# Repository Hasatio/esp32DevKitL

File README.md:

# ESP32-DEVKIT-L

The circuit taken as an example while designing the board [Olimex ESP32-Gateway](https://www.olimex.com/Products/IoT/ESP32/ESP32-GATEWAY)

## Revision 0

### Added:
- 1x TCA9548 mux IC
- 8x QWIIC connector
- 2x2 Molex connector for for external power supply
- 1x K7805-2000R3L or K7805-2000R3 for 5v convert
- Logo

### Changed:
- Type C
- ESP32-WROOM-32D model
- K7803-2000R3L or K7803-2000R3 for 5V to 3.3V convert
- Texts in pinout

## Revision 1

### Added:
- QWIIC connector pinout

## Revision 2

### Changed:
- Led GPIO33 to GPIO35
- PCA9548's SDA pin GPIO16 to GPIO33

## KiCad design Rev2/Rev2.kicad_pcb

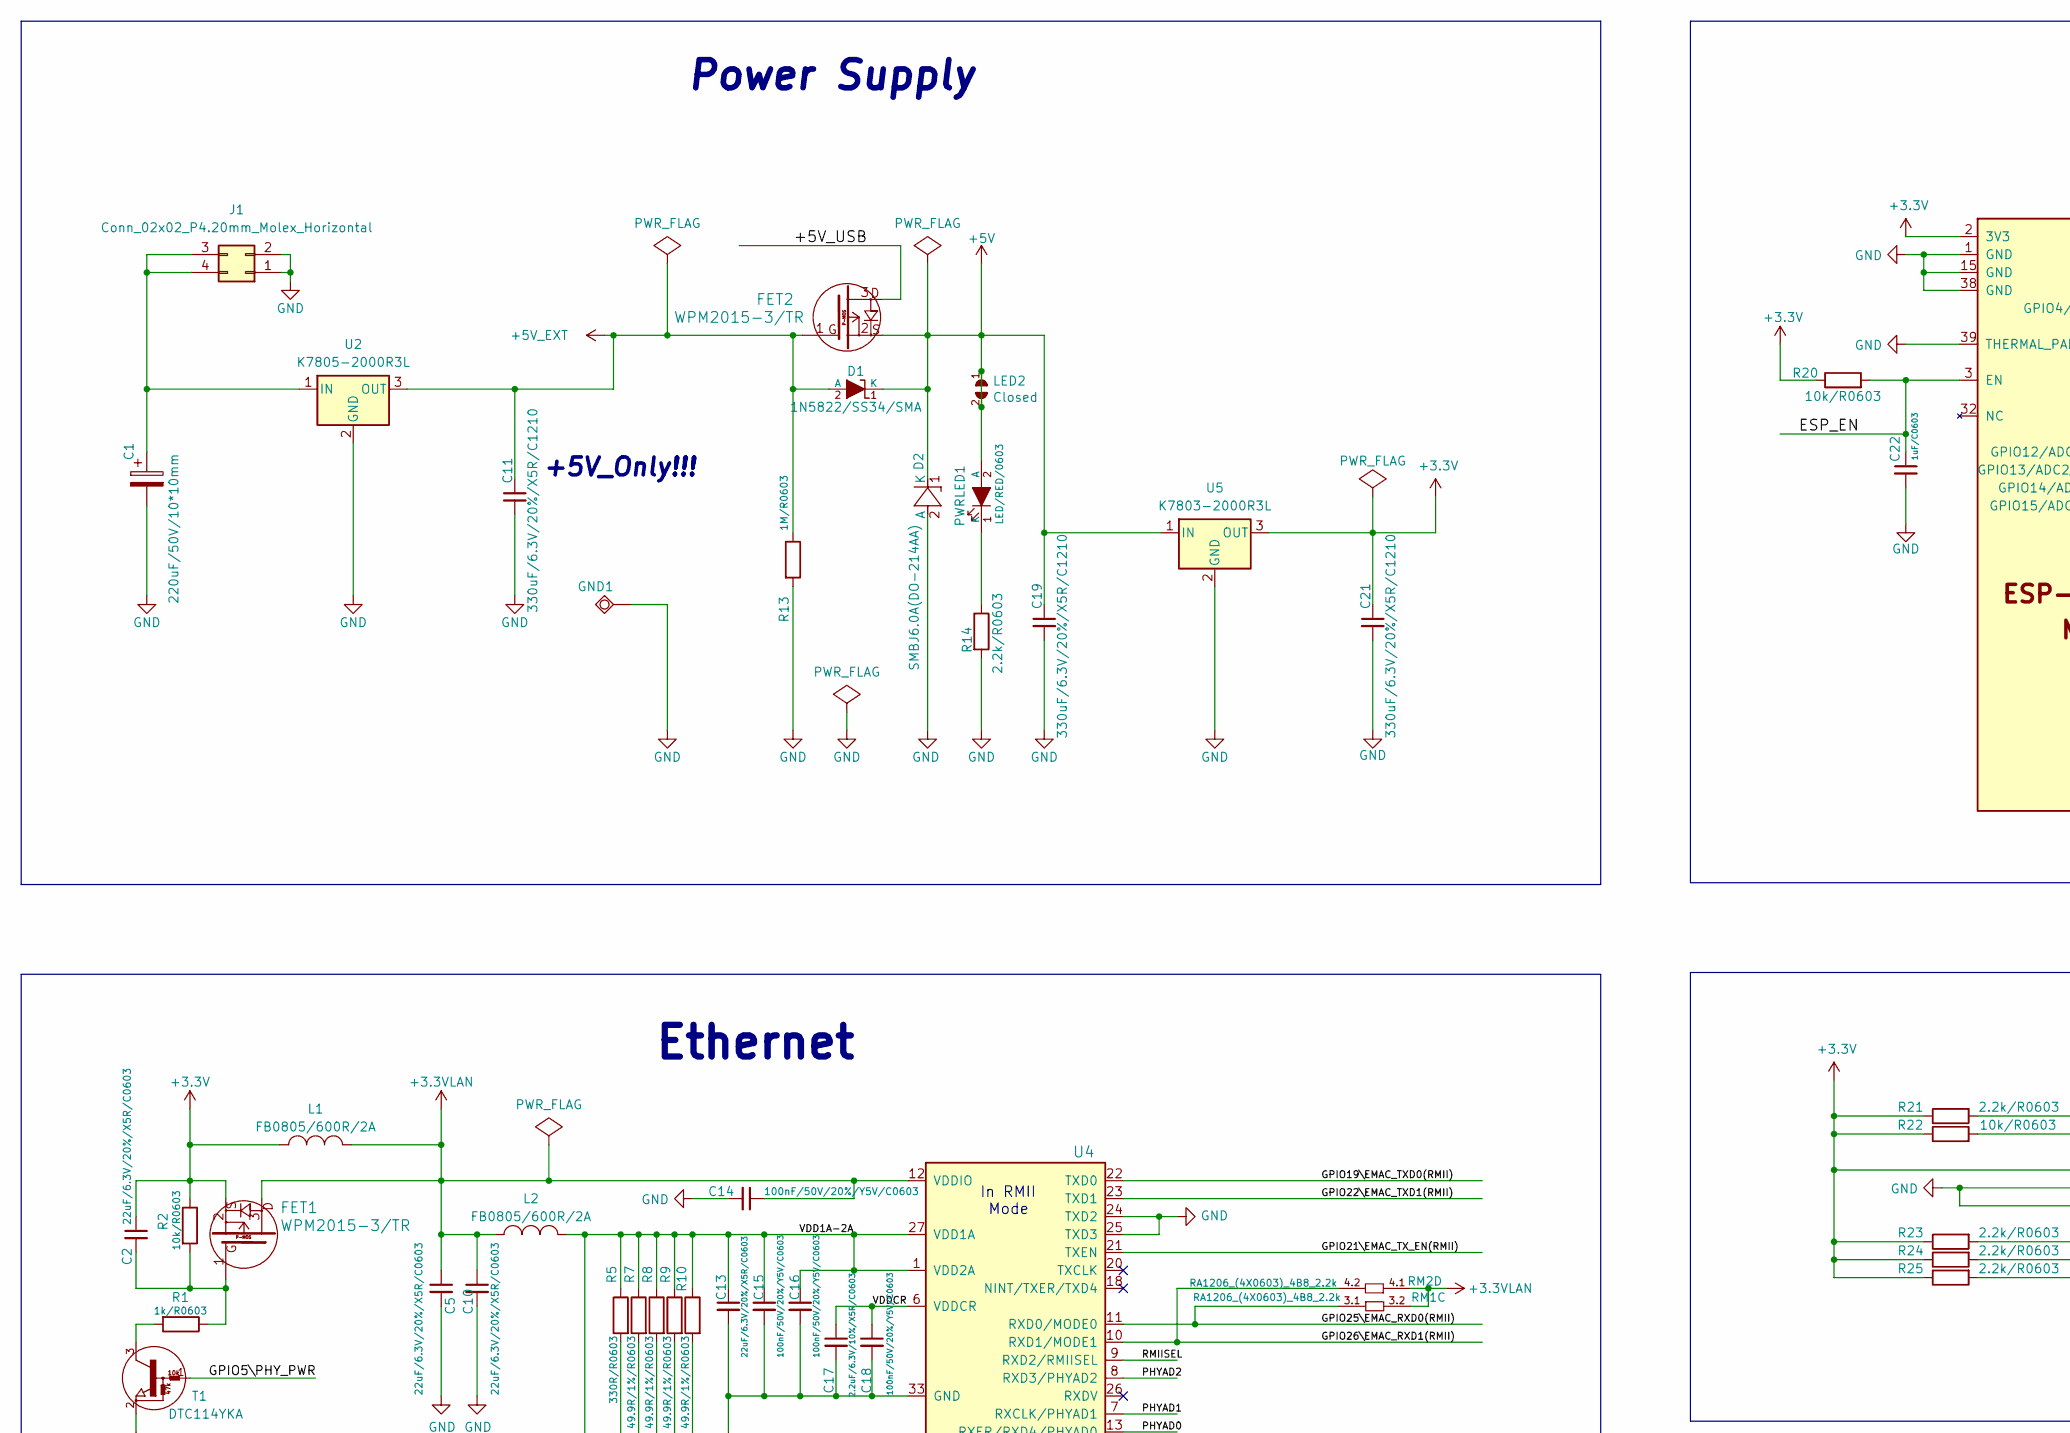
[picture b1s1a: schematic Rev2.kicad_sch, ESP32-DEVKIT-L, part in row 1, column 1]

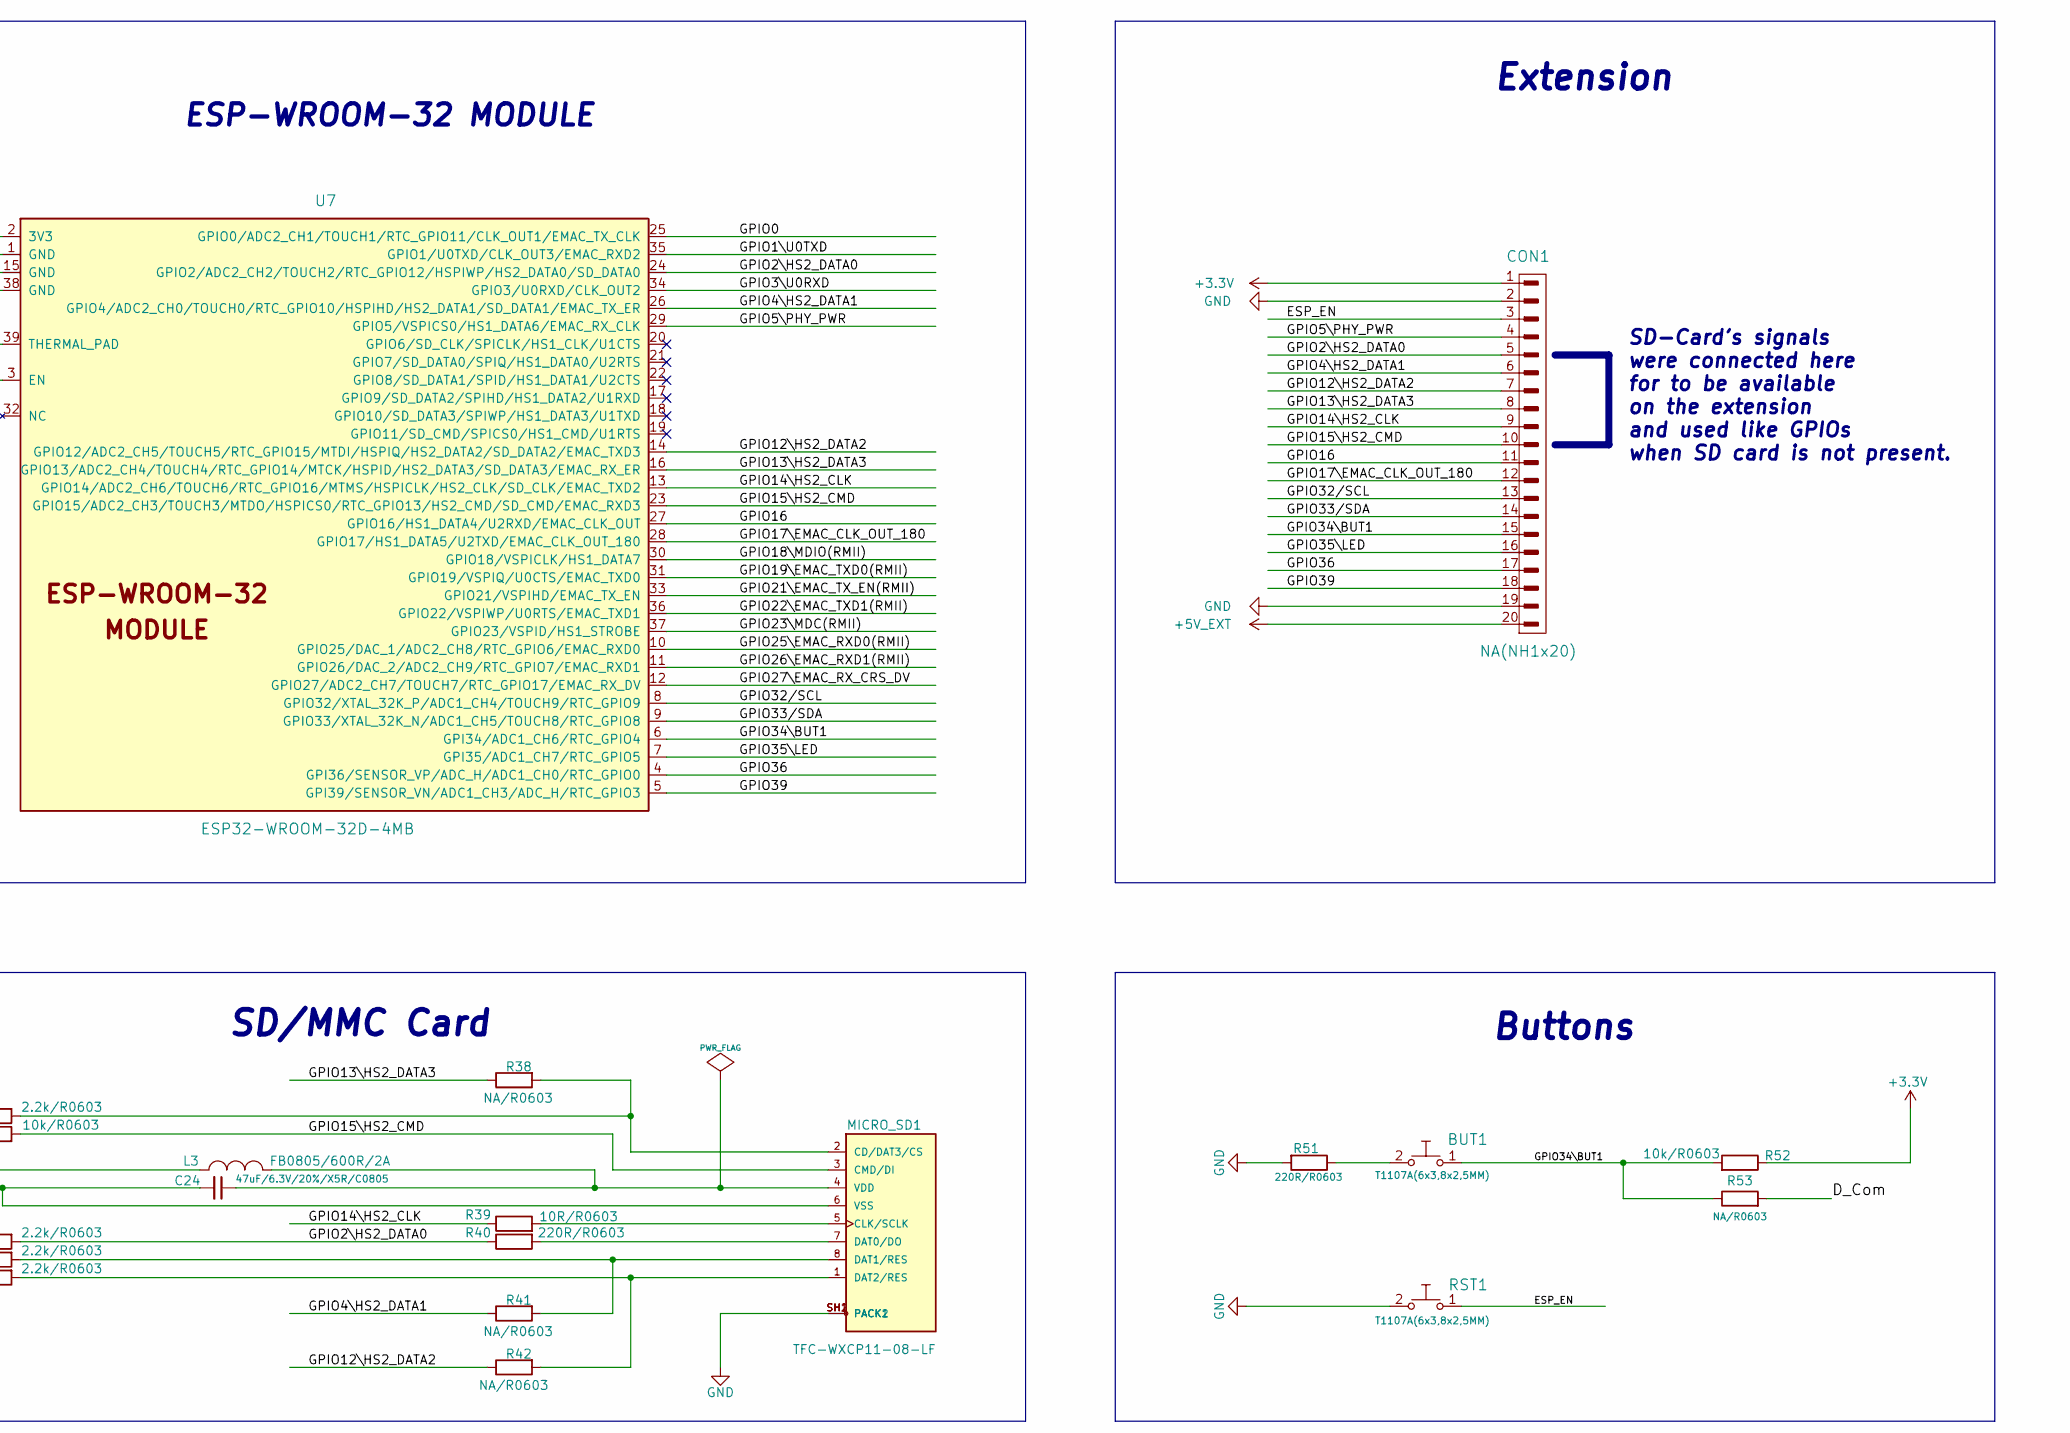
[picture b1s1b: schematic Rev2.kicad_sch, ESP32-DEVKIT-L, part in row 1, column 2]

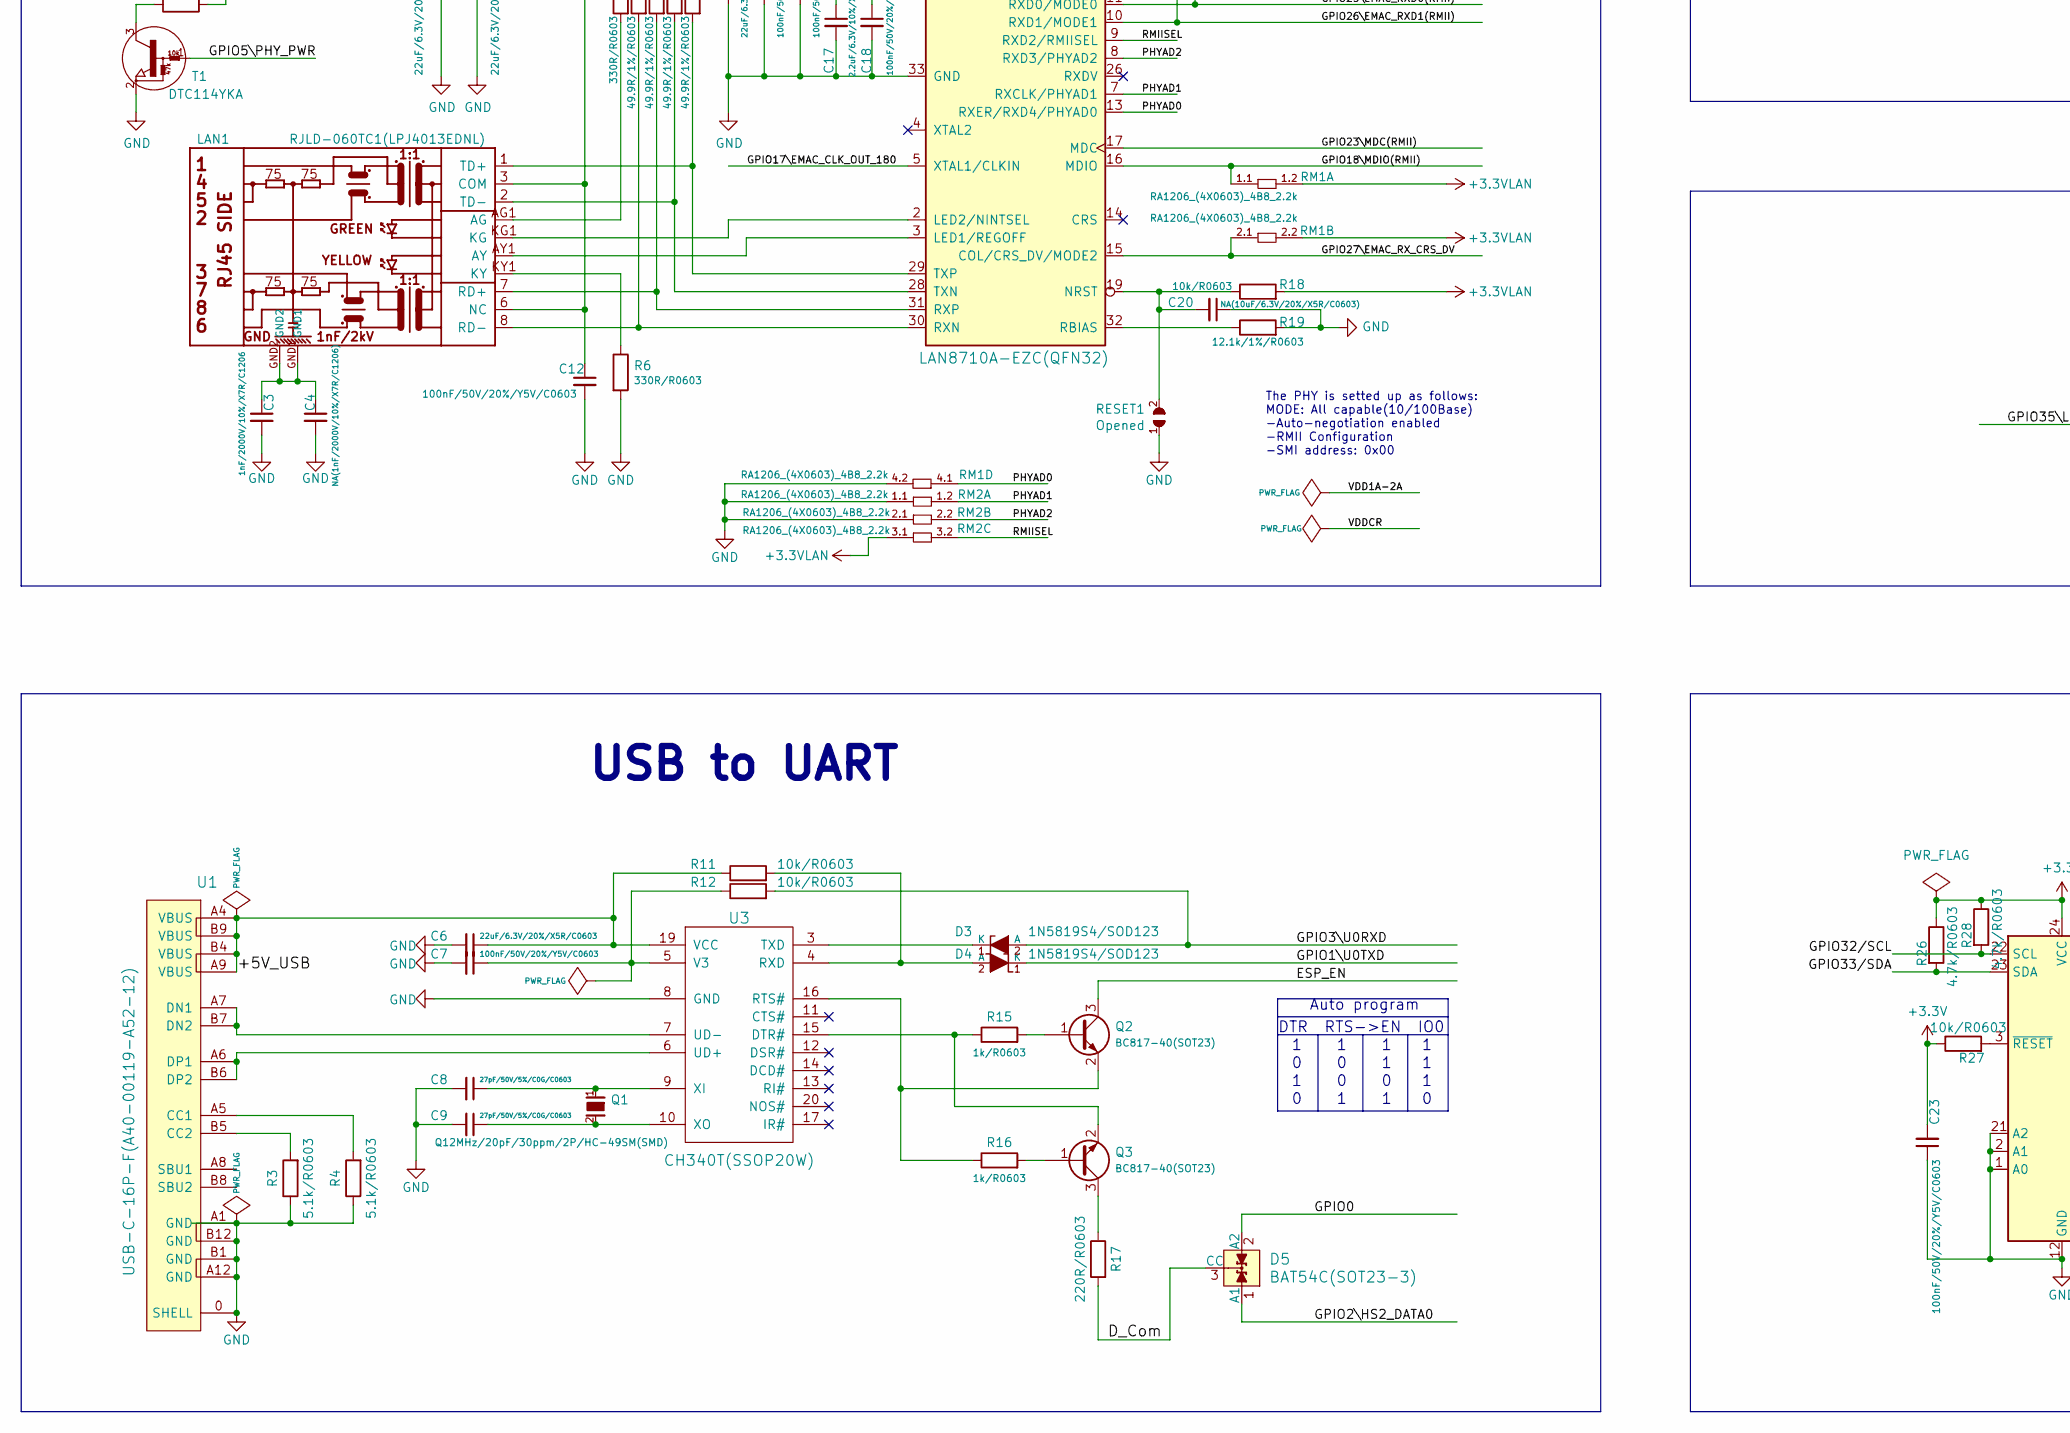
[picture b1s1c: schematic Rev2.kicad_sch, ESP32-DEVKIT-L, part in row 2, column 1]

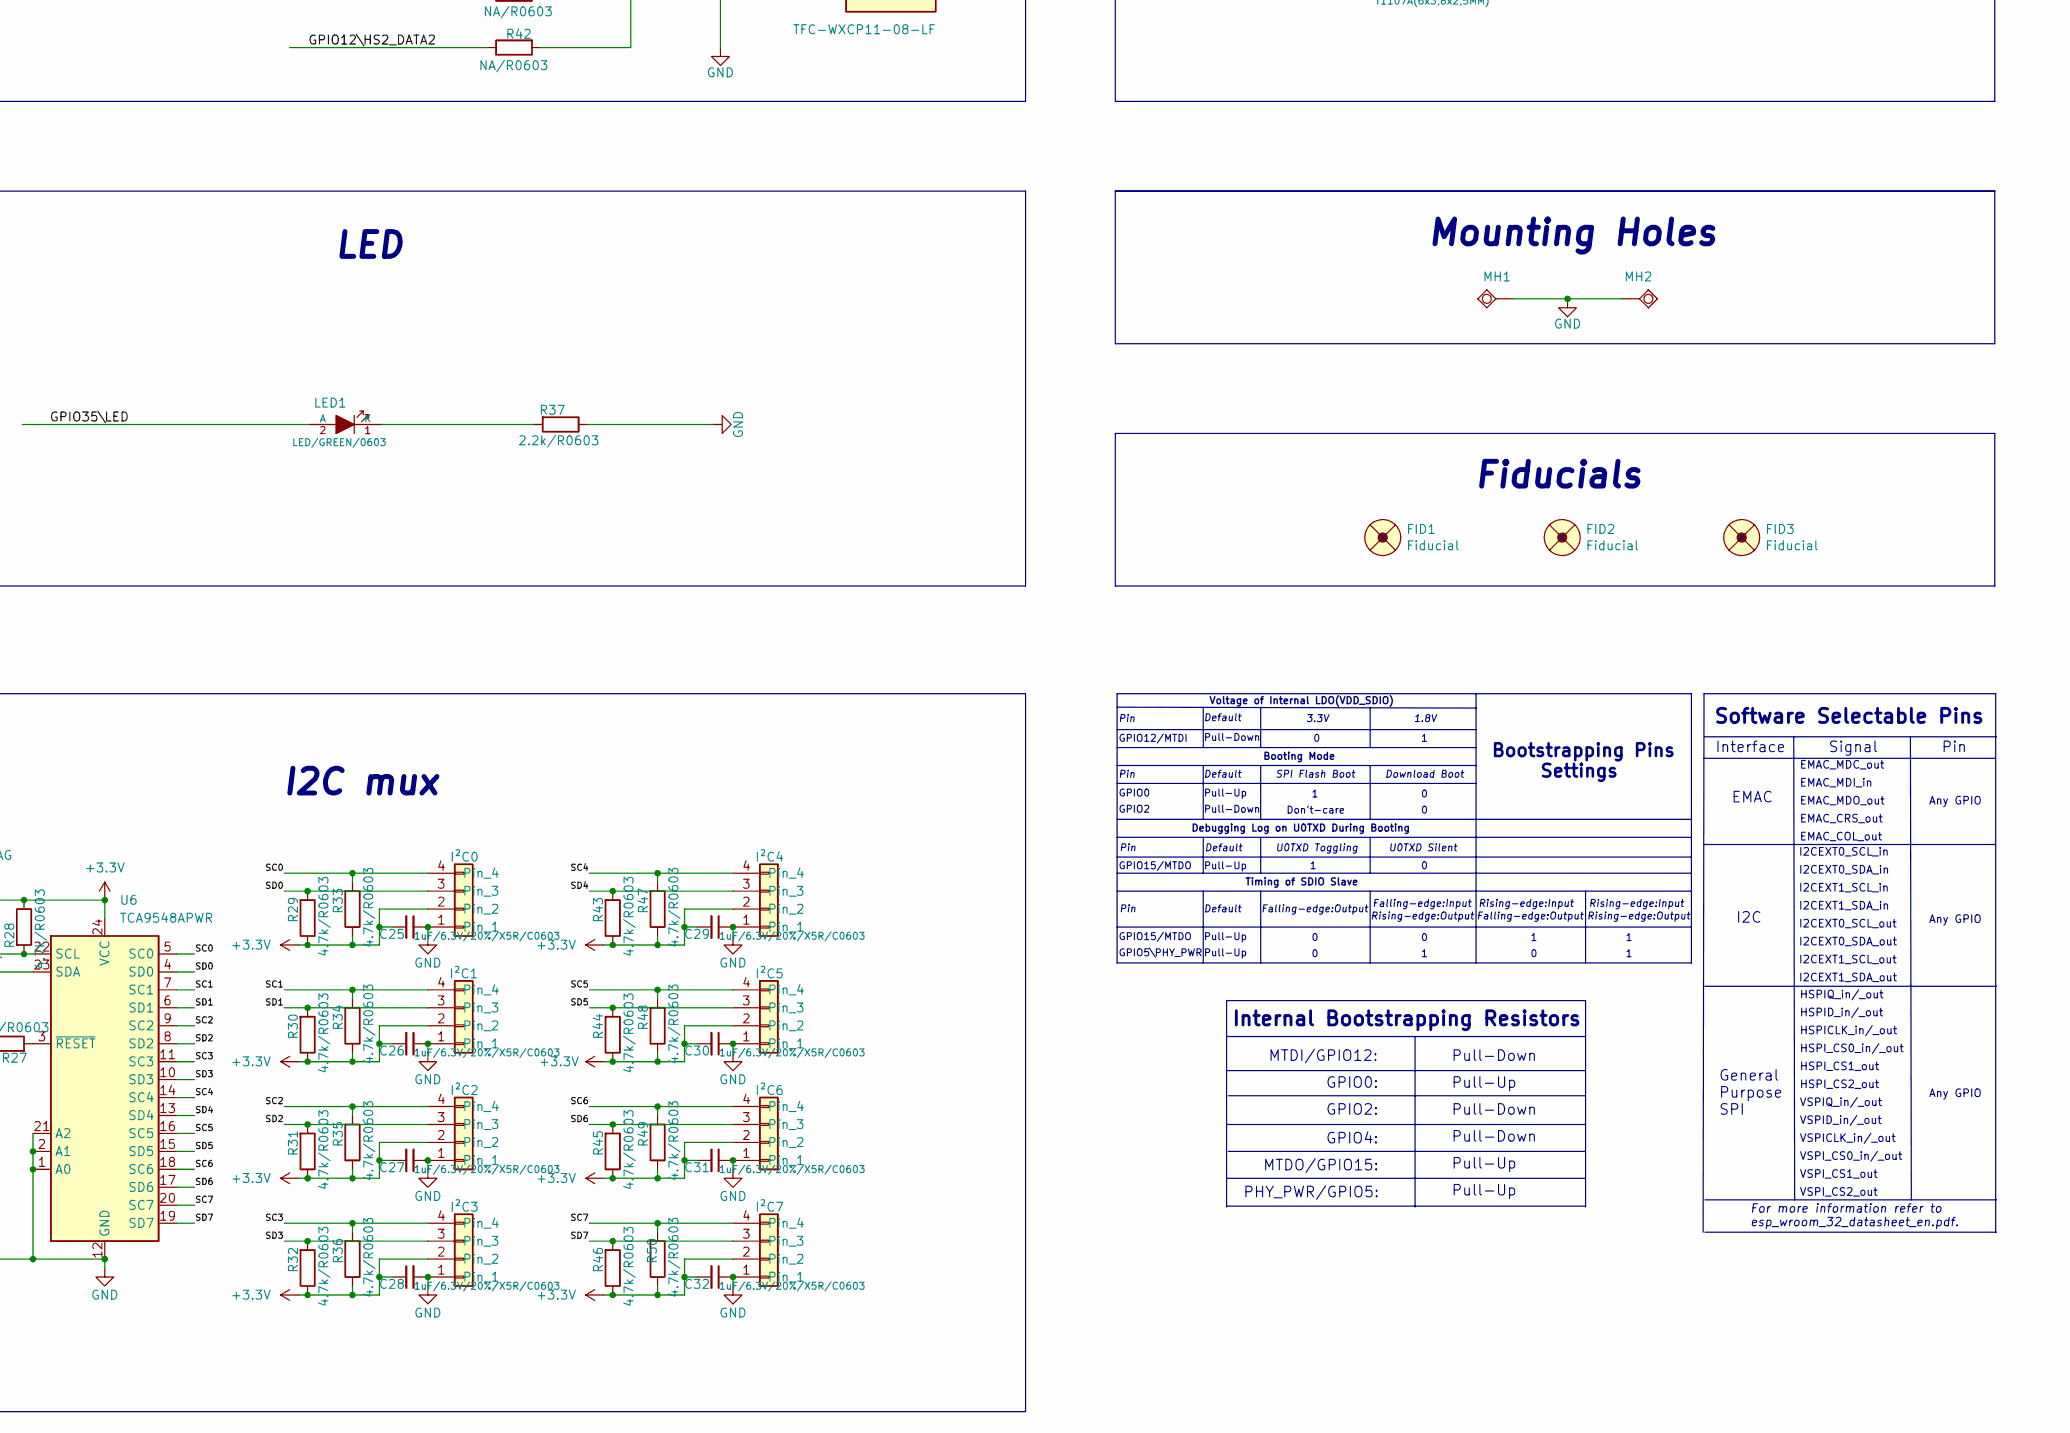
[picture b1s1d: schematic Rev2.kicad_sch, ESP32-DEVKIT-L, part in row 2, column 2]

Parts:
BUT1: T1107A(6x3,8x2,5MM)
C1: 220uF/50V/10*10mm; CP_Elec_10x10.5
C2, C5, C6, C10, C13: 22uF/6.3V/20%/X5R/C0603; 0603
C3: 1nF/2000V/10%/X7R/C1206; 1206
C4: NA(1nF/2000V/10%/X7R/C1206); 1206
C7, C12, C14, C15, C16, C18, C23: 100nF/50V/20%/Y5V/C0603; 0603
C8, C9: 27pF/50V/5%/C0G/C0603; 0603
C11, C19, C21: 330uF/6.3V/20%/X5R/C1210; 1210
C17: 2.2uF/6.3V/10%/X5R/C0603; 0603
C20: NA(10uF/6.3V/20%/X5R/C0603); 0603
C22: 1uF/C0603; 0603
C24: 47uF/6.3V/20%/X5R/C0805; 0805
C25, C26, C27, C28, C29, C30, C31, C32: 1uF/6.3V/20%/X5R/C0603; 0603
CON1: NA(NH1x20); HN1x20
D1: 1N5822/SS34/SMA; SMA-KA
D2: SMBJ6.0A(DO-214AA); DO214AA_1(K)-2(A)
D3, D4: 1N5819S4/SOD123; SOD-123_1C-2A_KA
D5: BAT54C(SOT23-3); SOT23-3
FET1, FET2: WPM2015-3/TR; SOT23
FID1, FID2, FID3: Fiducial; Fiducial1x3
GND1: TESTPAD; TESTPAD_40-ROUND
I²C0, I²C1, I²C2, I²C3, I²C4, I²C5, I²C6, I²C7: Conn_01x04_P1.00mm_Stemma qt/Qwiic; JST_SH_SM04B-SRSS-TB_1x04-1MP_P1.00mm_Horizontal
J1: Conn_02x02_P4.20mm_Molex_Horizontal; Molex_Mini-Fit_Jr_5569-04A1_2x02_P4.20mm_Horizontal
L1, L2, L3: FB0805/600R/2A; L_0805_5MIL_DWS
LAN1: RJLD-060TC1(LPJ4013EDNL); RJLBC-060TC1
LED1: LED/GREEN/0603; LED_0603_KA
LED2: Closed; SJ
MH1, MH2: Mounting_hole_Shield_3.3mm
MICRO_SD1: TFC-WXCP11-08-LF
PWRLED1: LED/RED/0603; LED_0603_KA
Q1: Q12MHz/20pF/30ppm/2P/HC-49SM(SMD); Q_49U3HMS
Q2, Q3: BC817-40(SOT23); SOT23
R1, R15, R16: 1k/R0603; 0603
R2, R11, R12, R18, R20, R22, R27, R52: 10k/R0603; 0603
R3, R4: 5.1k/R0603; 0603
R5, R6: 330R/R0603; 0603
R7, R8, R9, R10: 49.9R/1%/R0603; 0603
R13: 1M/R0603; 0603
R14, R21, R23, R24, R25, R37: 2.2k/R0603; 0603
R17, R40, R51: 220R/R0603; 0603
R19: 12.1k/1%/R0603; 0603
R26, R28, R29, R30, R31, R32, R33, R34, R35, R36, R43, R44, R45, R46, R47, R48, R49, R50: 4.7k/R0603; 0603
R38, R41, R42, R53: NA/R0603; 0603
R39: 10R/R0603; 0603
RESET1: Opened; SJ
RM1, RM2: RA1206_(4X0603)_4B8_2.2k; R_MATRIX_4
RST1: T1107A(6x3,8x2,5MM)
T1: DTC114YKA; SOT23
U1: USB-C-16P-F(A40-00119-A52-12); USB2.0_TYPE-C(A40-00119-A52-12)
U2: K7805-2000R3L; Converter_DCDC_RECOM_R-78HB-0.5L_THT
U3: CH340T(SSOP20W); SSOP-20W
U4: LAN8710A-EZC(QFN32); QFN32_EP(33)_5.00x5.00x0.90mm_Pitch_0.50mm
U5: K7803-2000R3L; Converter_DCDC_RECOM_R-78HB-0.5L_THT
U6: TCA9548APWR; TSSOP-24_4.4x7.8mm_P0.65mm
U7: ESP32-WROOM-32D-4MB; ESP-WROOM-32_MODULE

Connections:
+3.3VLAN: C5.1, C10.1, C14.1, FET1.3, L1.2, L2.1, R18.2, RM1.1.2, RM1.2.2, RM1.3.2, RM2.3.1, RM2.4.1, U4.12 (VDDIO)
+3V3: C2.1, C21.1, C23.2, C25.2, C26.2, C27.2, C28.1, C29.2, C30.2, C31.2, C32.2, CON1.1, FET1.2, I²C0.2, I²C1.2, I²C2.2, I²C3.2, I²C4.2, I²C5.2, I²C6.2, I²C7.2, L1.1, L3.1, R2.1, R20.1, R21.1, R22.1, R23.1, R24.1, R25.1, R26.1, R27.1, R28.1, R29.1, R30.1, R31.1, R32.1, R33.1, R34.1, R35.1, R36.1, R43.1, R44.1, R45.1, R46.1, R47.1, R48.1, R49.1, R50.1, R52.1, U5.3 (OUT), U6.24 (VCC), U7.2 (3V3)
+5V: C19.1, D1.1 (K), D2.1 (K), FET2.2, LED2.1, LED2.2, PWRLED1.2 (A), U5.1 (IN); also elsewhere on the board
+5V_EXT: C11.1, CON1.20, D1.2 (A), FET2.1, R13.1, U2.3 (OUT)
/+5V_USB: C6.1, FET2.3, R11.1, U1.A4 (VBUS), U1.A9 (VBUS), U1.B4 (VBUS), U1.B9 (VBUS), U3.19 (VCC)
/D_Com: D5.3 (CC), R17.2, R53.2
/ESP_EN: C22.1, CON1.3, Q2.3 (C), R20.2, RST1.1, U7.3 (EN)
/GPIO0: D5.2 (A2), U7.25 (GPIO0/ADC2_CH1/TOUCH1/RTC_GPIO11/CLK_OU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)
/GPIO1\U0TXD: D4.1 (K), U7.35 (GPIO1/U0TXD/CLK_OUT3/EMAC_RXD2)
/GPIO2\HS2_DATA0: CON1.5, D5.1 (A1), R23.2, R40.1, U7.24 (GPIO2/ADC2_CH2/TOUCH2/RTC_GPIO12/HSPIWP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)
/GPIO3\U0RXD: D3.2 (A), R12.2, U7.34 (GPIO3/U0RXD/CLK_OUT2)
/GPIO4\HS2_DATA1: CON1.6, R41.1, U7.26 (GPIO4/ADC2_CH0/TOUCH0/RTC_GPIO10/HSPIHD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)
/GPIO5\PHY_PWR: CON1.4, T1.1 (B), U7.29 (GPIO5/VSPICS0/HS1_DATA6/EMAC_RX_CLK)
/GPIO12\HS2_DATA2: CON1.7, R42.1, U7.14 (GPIO12/ADC2_CH5/TOUCH5/RTC_GPIO15/MTDI/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)
/GPIO13\HS2_DATA3: CON1.8, R38.1, U7.16 (GPIO13/ADC2_CH4/TOUCH4/RTC_GPIO14/MTCK/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)
/GPIO14\HS2_CLK: CON1.9, R39.1, U7.13 (GPIO14/ADC2_CH6/TOUCH6/RTC_GPIO16/MTMS/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)
/GPIO15\HS2_CMD: CON1.10, MICRO_SD1.3 (CMD/DI), R22.2, U7.23 (GPIO15/ADC2_CH3/TOUCH3/MTDO/HSPICS0/RTC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)
/GPIO16: CON1.11, U7.27 (GPIO16/HS1_DATA4/U2RXD/EMAC_CLK_OUT)
/GPIO17\EMAC_CLK_OUT_180: CON1.12, U4.5 (XTAL1/CLKIN), U7.28 (GPIO17/HS1_DATA5/U2TXD/EMAC_CLK_OUT_180)
/GPIO18\MDIO(RMII): RM1.1.1, U4.16 (MDIO), U7.30 (GPIO18/VSPICLK/HS1_DATA7)
/GPIO19\EMAC_TXD0(RMII): U4.22 (TXD0), U7.31 (GPIO19/VSPIQ/U0CTS/EMAC_TXD0)
/GPIO21\EMAC_TX_EN(RMII): U4.21 (TXEN), U7.33 (GPIO21/VSPIHD/EMAC_TX_EN)
/GPIO22\EMAC_TXD1(RMII): U4.23 (TXD1), U7.36 (GPIO22/VSPIWP/U0RTS/EMAC_TXD1)
/GPIO23\MDC(RMII): U4.17 (MDC), U7.37 (GPIO23/VSPID/HS1_STROBE)
/GPIO25\EMAC_RXD0(RMII): RM1.3.1, U4.11 (RXD0/MODE0), U7.10 (GPIO25/DAC_1/ADC2_CH8/RTC_GPIO6/EMAC_RX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)
/GPIO26\EMAC_RXD1(RMII): RM2.4.2, U4.10 (RXD1/MODE1), U7.11 (GPIO26/DAC_2/ADC2_CH9/RTC_GPIO7/EMAC_RX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)
/GPIO27\EMAC_RX_CRS_DV: RM1.2.1, U4.15 (COL/CRS_DV/MODE2), U7.12 (GPIO27/ADC2_CH7/TOUCH7/RTC_GPIO17/EMAC_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)
/GPIO32/SCL: CON1.13, R28.2, U6.22 (SCL), U7.8 (GPIO32/XTAL_32K_P/ADC1_CH4/TOUCH9/RTC_G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)
/GPIO33/SDA: CON1.14, R26.2, U6.23 (SDA), U7.9 (GPIO33/XTAL_32K_N/ADC1_CH5/TOUCH8/RTC_G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)
/GPIO34\BUT1: BUT1.1, CON1.15, R52.2, R53.1, U7.6 (GPI34/ADC1_CH6/RTC_GPIO4)
/GPIO35\LED: CON1.16, LED1.2 (A), U7.7 (GPI35/ADC1_CH7/RTC_GPIO5)
/GPIO36: CON1.17, U7.4 (GPI36/SENSOR_VP/ADC_H/ADC1_CH0/RTC_GPIO0)
/GPIO39: CON1.18, U7.5 (GPI39/SENSOR_VN/ADC1_CH3/ADC_H/RTC_GPIO3)
/PHYAD0: RM1.4.1, U4.13 (RXER/RXD4/PHYAD0)
/PHYAD1: RM2.1.2, U4.7 (RXCLK/PHYAD1)
/PHYAD2: RM2.2.2, U4.8 (RXD3/PHYAD2)
/RMIISEL: RM2.3.2, U4.9 (RXD2/RMIISEL)
/SC0: I²C0.4, R33.2, U6.5 (SC0)
/SC1: I²C1.4, R34.2, U6.7 (SC1)
/SC2: I²C2.4, R35.2, U6.9 (SC2)
/SC3: I²C3.4, R36.2, U6.11 (SC3)
/SC4: I²C4.4, R47.2, U6.14 (SC4)
/SC5: I²C5.4, R48.2, U6.16 (SC5)
/SC6: I²C6.4, R49.2, U6.18 (SC6)
/SC7: I²C7.4, R50.2, U6.20 (SC7)
/SD0: I²C0.3, R29.2, U6.4 (SD0)
/SD1: I²C1.3, R30.2, U6.6 (SD1)
/SD2: I²C2.3, R31.2, U6.8 (SD2)
/SD3: I²C3.3, R32.2, U6.10 (SD3)
/SD4: I²C4.3, R43.2, U6.13 (SD4)
/SD5: I²C5.3, R44.2, U6.15 (SD5)
/SD6: I²C6.3, R45.2, U6.17 (SD6)
/SD7: I²C7.3, R46.2, U6.19 (SD7)
/VDD1A-2A: C12.1, C13.1, C15.1, C16.1, L2.2, LAN1.3 (COM), LAN1.6 (NC), R5.1, R7.1, R8.1, R9.1, R10.1, U4.1 (VDD2A), U4.27 (VDD1A)
/VDDCR: C17.1, C18.1, U4.6 (VDDCR)
GND: C1.2, C3.2, C4.2, C5.2, C6.2, C7.2, C8.2, C9.2, C10.2, C11.2, C12.2, C13.2, C14.2, C15.2, C16.2, C17.2, C18.2, C19.2, C20.1, C21.2, C22.2, C23.1, C24.2, C25.1, C26.1, C27.1, C28.2, C29.1, C30.1, C31.1, C32.1, CON1.2, CON1.19, D2.2 (A), GND1.1 (Pad), I²C0.1, I²C1.1, I²C2.1, I²C3.1, I²C4.1, I²C5.1, I²C6.1, I²C7.1, J1.1, J1.2, MH1.GND1, MH2.GND1, MICRO_SD1.6 (VSS), MICRO_SD1.SH1 (PACK1), MICRO_SD1.SH2 (PACK2), R3.1, R4.1, R6.2, R13.2, R14.2, R19.2, R37.1, R51.2, RESET1.1, RM1.4.2, RM2.1.1, RM2.2.1, RST1.2, T1.2 (E), U1.0 (SHELL), U1.A1 (GND), U1.A12 (GND), U1.B1 (GND), U1.B12 (GND), U2.2 (GND), U3.8 (GND), U4.24 (TXD2), U4.25 (TXD3), U4.33 (GND), U5.2 (GND), U6.1 (A0), U6.2 (A1), U6.12 (GND), U6.21 (A2), U7.1 (GND), U7.15 (GND), U7.38 (GND), U7.39 (THERMAL_PAD); also elsewhere on the board
unnamed: BUT1.2, R51.1
unnamed: C2.2, FET1.1, R1.1, R2.2
unnamed: C3.1, C4.1, LAN1.GND1, LAN1.GND2
unnamed: D3.1 (K), U3.3 (TXD)
unnamed: D4.2 (A), R11.2, U3.4 (RXD)
unnamed: C1.1, J1.3, J1.4, U2.1 (IN)
unnamed: LAN1.AG1 (AG), R5.2
unnamed: LAN1.AY1 (AY), U4.3 (LED1/REGOFF)
unnamed: LAN1.KG1 (KG), U4.2 (LED2/NINTSEL)
unnamed: LAN1.KY1 (KY), R6.1
unnamed: LAN1.7 (RD+), R8.2, U4.31 (RXP)
unnamed: LAN1.8 (RD-), R7.2, U4.30 (RXN)
unnamed: LAN1.1 (TD+), R10.2, U4.29 (TXP)
unnamed: LAN1.2 (TD-), R9.2, U4.28 (TXN)
unnamed: LED1.1 (K), R37.2
unnamed: MICRO_SD1.2 (CD/DAT3/CS), R21.2, R38.2
unnamed: MICRO_SD1.5 (CLK/SCLK), R39.2
unnamed: MICRO_SD1.7 (DAT0/DO), R40.2
unnamed: MICRO_SD1.8 (DAT1/RES), R24.2, R41.2
unnamed: MICRO_SD1.1 (DAT2/RES), R25.2, R42.2
unnamed: C24.1, L3.2, MICRO_SD1.4 (VDD)
unnamed: PWRLED1.1 (K), R14.1
unnamed: Q2.1 (B), R15.2
unnamed: Q2.2 (E), R16.1, U3.16 (RTS#)
unnamed: Q3.1 (B), R16.2
unnamed: Q3.3 (C), R17.1
unnamed: Q3.2 (E), R15.1, U3.15 (DTR#)
unnamed: R1.2, T1.3 (C)
unnamed: R4.2, U1.A5 (CC1)
unnamed: R3.2, U1.B5 (CC2)
unnamed: U1.A7 (DN1), U1.B7 (DN2), U3.7 (UD-)
unnamed: U1.A6 (DP1), U1.B6 (DP2), U3.6 (UD+)
unnamed: C7.1, R12.1, U3.5 (V3)
unnamed: C8.1, Q1.1, U3.9 (XI)
unnamed: C9.1, Q1.2, U3.10 (XO)
unnamed 91: C20.2, R18.1, RESET1.2, U4.19 (NRST); also elsewhere on the board
unnamed: R19.1, U4.32 (RBIAS)
unnamed: R27.2, U6.3 (~RESET)

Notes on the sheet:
EMAC
Any GPIO
LED
GPIO0:
Power Supply
+5V_Only!!!
Internal Bootstrapping Resistors
Debugging Log on U0TXD During Booting
Auto program
Pull-Up
GPIO15/MTDO
Rising-edge:Output
For more information refer to esp_wroom_32_datasheet_en.pdf.
I2C mux
VSPIQ_in/_out
SD/MMC Card
USB to UART
Software Selectable Pins
Rising-edge:Input
Pull-Down
Default
VSPI_CS0_in/_out
VSPI_CS1_out
Pin
Falling-edge:Output
I2CEXT1_SDA_in
EMAC_MDO_out
Voltage of Internal LDO(VDD_SDIO)
SD-Card's signals were connected here for to be available on the extension and used like GPIOs when SD card is not present.
Extension
Booting Mode
I2CEXT0_SDA_in
1.8V
3.3V
U0TXD Silent
I2C
GPIO2
GPIO5\PHY_PWR
Buttons
EMAC_COL_out

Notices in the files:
Rev2/Rev2.kicad_pcb:
(C) 2023
